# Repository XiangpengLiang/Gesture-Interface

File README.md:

Gesture Interface Glove<br>
University of Glasgow<br>
Real Time Embedded Programming: Raspberry PI Assignment
=
[Demonstration video](https://youtu.be/rbo2YH-eyuY)
=
Tutor: Bernd Porr<br>
Students: Xiangpeng Liang, Zhong Lu, Chenhan Ye
-

Introduction
-
   This project aims to attach flex sensors to the glove, and drive the sensor to deform through the bending of the finger, displaying the physical input value on the screen. After calibration, simple gesture games (Rock-Paper-Scissor) can be realized in the current system. Also, this system is suitable for exploitation for various gesture control applications.<br>
   Sampling rate: 441Hz for five sensors and 2205Hz for one sensor<br>
   Power coumption: 3.3W

Making it work
-
Hardware: Raspberry Pi B+,PCB, 5 [flex sensors](http://www.robotshop.com/uk/22-10k-flexible-sensor.html?gclid=CjwKEAjwz9HHBRDbopLGh-afzB4SJABY52oFbqccsSkHznvQcYiAtR8d1_bVHjz4ba2aHKLVBFFj0RoCImXw_wcB) on a glove<br>
System: 2017-03-02-raspbian-jessie-lite<br>
Install: Git, xorg<br>
Library: bcm2835, Qwt, Qt 4.8

To clone the git repository:
-
    git clone https://github.com/pppxp/Gesture-Interface.git

To build:
-
    cd Gesture-Interaface
    qmake
    make

To run (assuming you are logged into the RPi over ssh and no X-server is running):

    startx ./Gesture

=================================

Qt is a cross platform framework for developing graphical applications, for more information please visit the links below:
* [Qt Homepage](http://qt-project.org/)
* [Qt 4.8 Class List](http://qt-project.org/doc/qt-4.8/classes.html)
* [Wikpedia](http://en.wikipedia.org/wiki/Qt_%28framework%29)
* [Signals and Slots](http://qt-project.org/doc/qt-4.8/signalsandslots.html)

Qwt is a technical widget library based on Qt, please see:
* [Qwt Hompage](http://qwt.sourceforge.net/)

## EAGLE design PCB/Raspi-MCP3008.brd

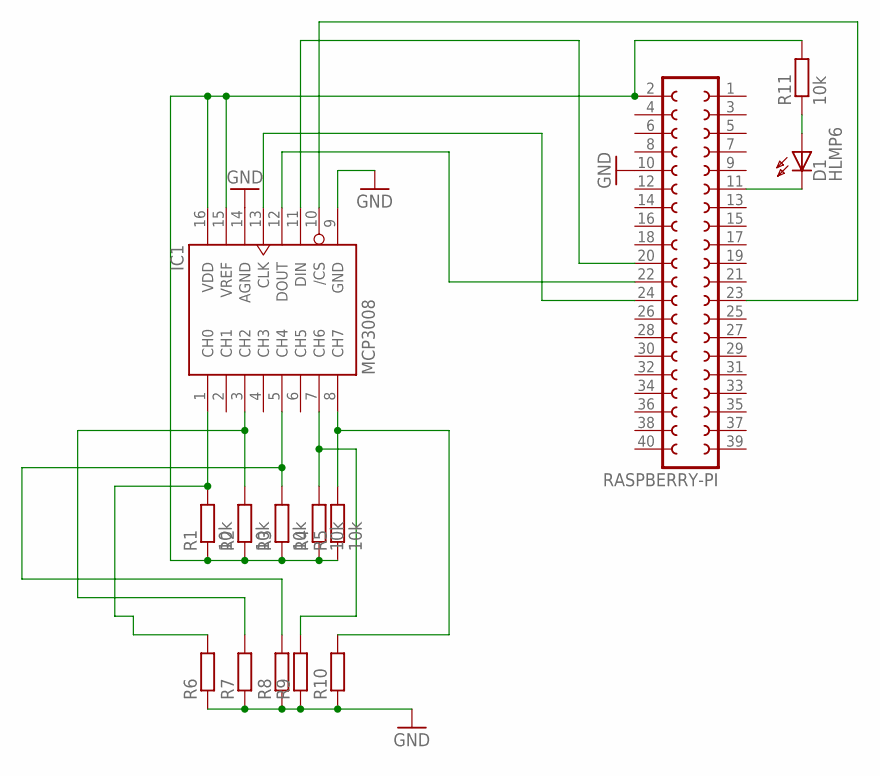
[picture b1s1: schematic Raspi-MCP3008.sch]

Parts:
D1: HLMP6
IC1: MCP3008; DIL16
R1, R2, R3, R4, R5, R11: 10k; 0207/10
R6, R7, R8, R9, R10: R-EU_0204/2V; 0204V
RASPBERRY-PI: FE20-2

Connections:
GND: IC1.9 (GND), IC1.14 (AGND), R6.1, R7.1, R8.1, R9.1, R10.1, RASPBERRY-PI.10
unnamed: D1.A, R11.1
unnamed: D1.K, RASPBERRY-PI.11
unnamed: IC1.13 (CLK), RASPBERRY-PI.24
unnamed: IC1.12 (DOUT), RASPBERRY-PI.22
unnamed: IC1.11 (DIN), RASPBERRY-PI.20
unnamed: IC1.10 (/CS), RASPBERRY-PI.23
unnamed: IC1.3 (CH2), R2.2, R7.2
unnamed: IC1.1 (CH0), R1.2, R6.2
unnamed: IC1.5 (CH4), R3.2, R8.2
unnamed: IC1.7 (CH6), R4.2, R9.2
unnamed: IC1.8 (CH7), R5.2, R10.2
unnamed: IC1.15 (VREF), IC1.16 (VDD), R1.1, R2.1, R3.1, R4.1, R5.1, R11.2, RASPBERRY-PI.2

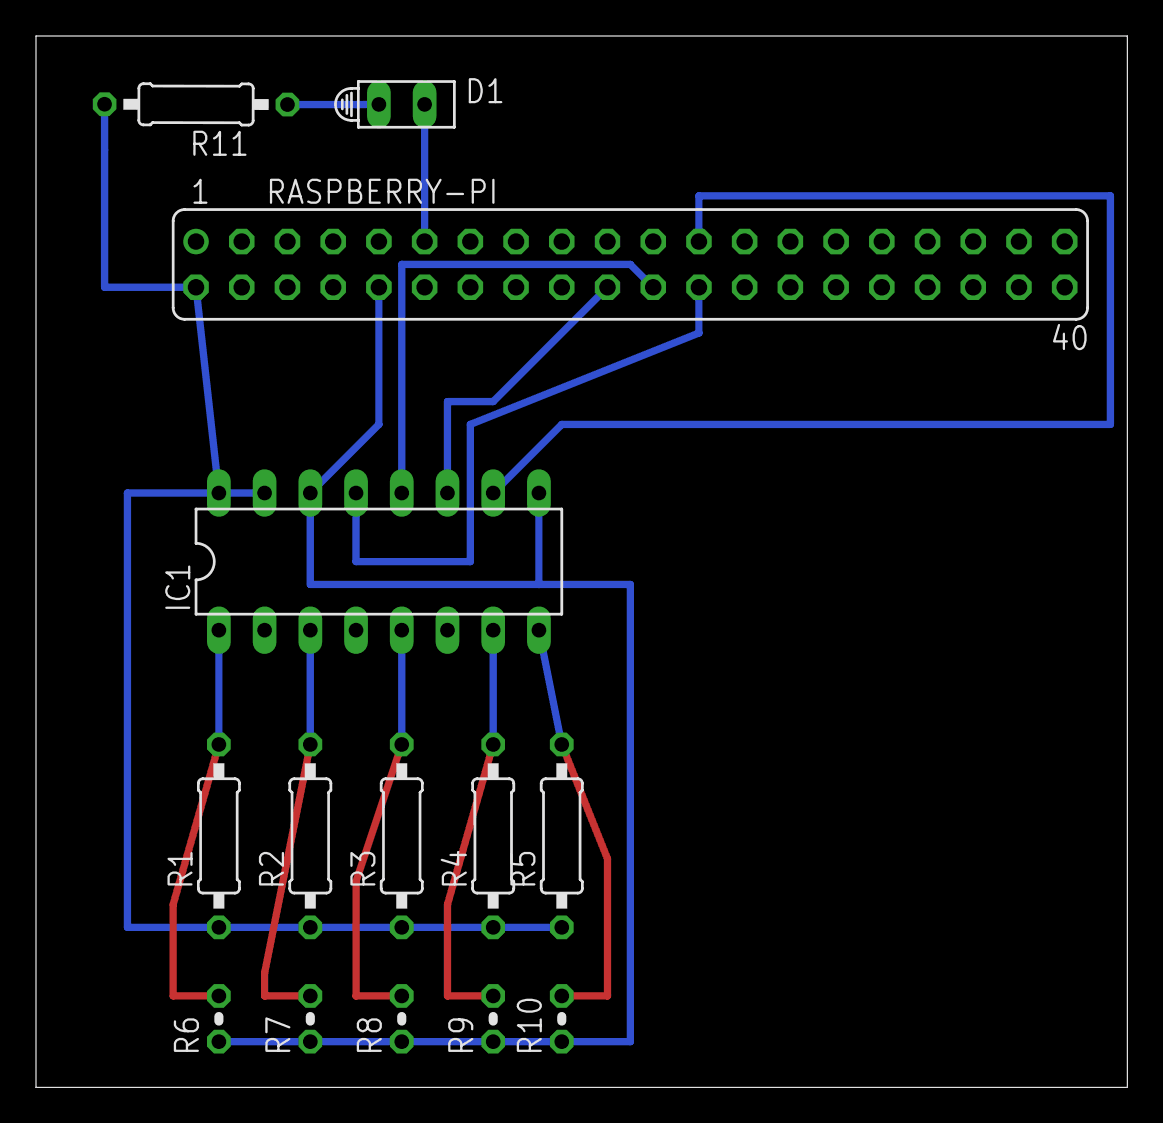
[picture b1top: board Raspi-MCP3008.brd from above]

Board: 2 copper layers, 60.6 x 58.4 mm, 14 parts (0 on the bottom side), 13 nets.

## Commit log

2017-02-28 1
    2
2017-03-07 SPI TEST
2017-03-08 1
    1
2017-03-09 Voltage Measurement
    MCP3008
2017-03-17 Added graphical display
2017-03-18 A voltage display programm for single Flex sensor
    Libraries:
    bcm2835
    QT
    Qwt
    RUN:
    make distclean
2017-03-18 Revert "A voltage display programm for single Flex sensor"
    This reverts commit f7a173967c9b0cc1ec8b09adbeec7638fbcea93a.
2017-03-18 Revert "Revert "A voltage display programm for single Flex sensor""
    This reverts commit c6185949f550405a9ea1d9f6ce988926556f2b69.
2017-03-18 A voltage display programm for single Flex sensor
2017-04-02 Increase the number of input to 5.
    Enable 5 ADC channels, display 5 output on the interface.
2017-04-10 Fixed the bugs in sending and receiving data
2017-04-12 Many big changes. Finally it works.
2017-04-12 Add LICENSE
2017-04-14 Improve sampling rate; Rearrange the whole program; Add labels
2017-04-14 Put all image into a folder
2017-04-16 Add introduction in main
2017-04-16 Add PCB design files
